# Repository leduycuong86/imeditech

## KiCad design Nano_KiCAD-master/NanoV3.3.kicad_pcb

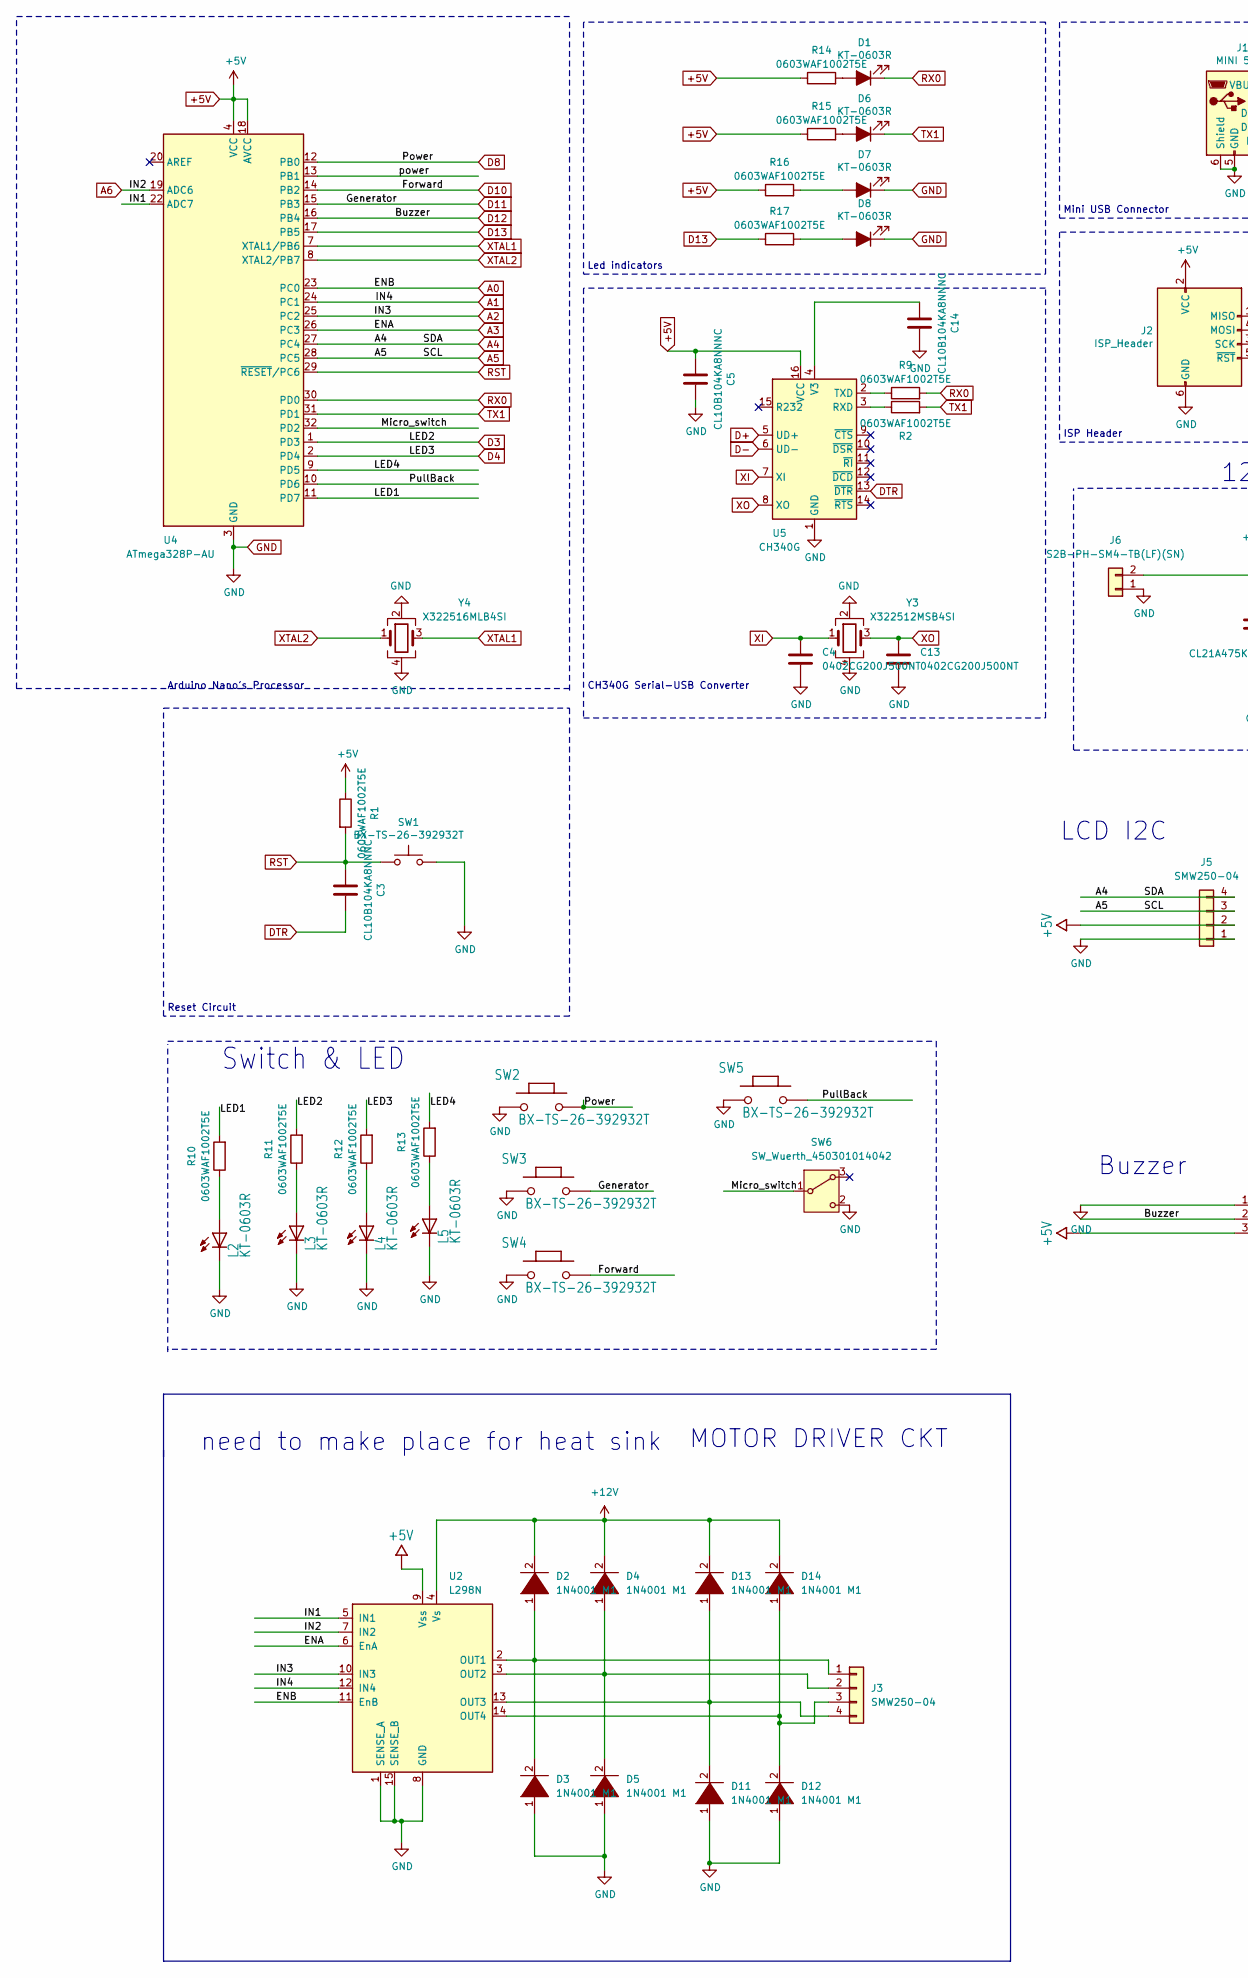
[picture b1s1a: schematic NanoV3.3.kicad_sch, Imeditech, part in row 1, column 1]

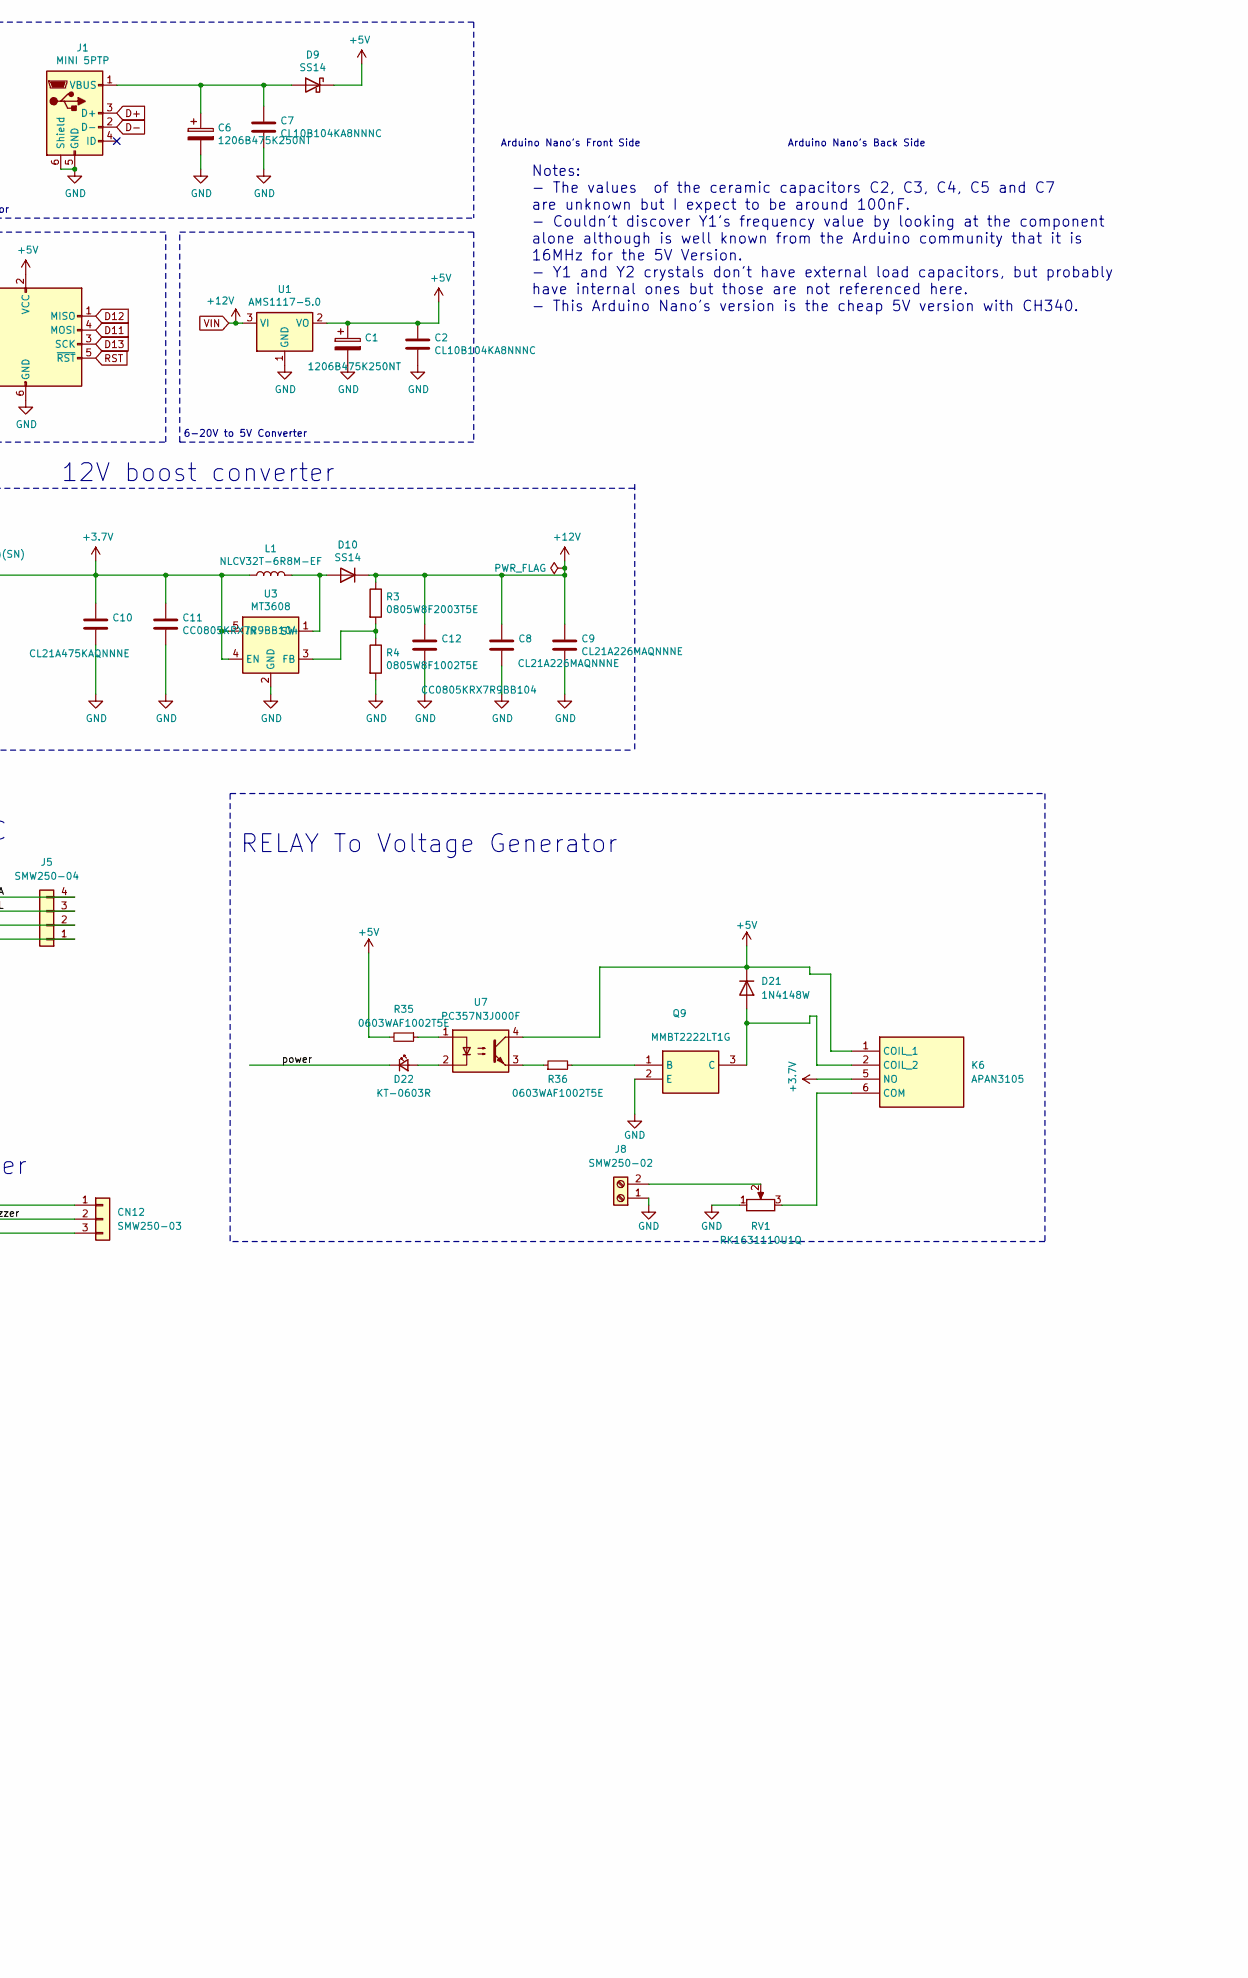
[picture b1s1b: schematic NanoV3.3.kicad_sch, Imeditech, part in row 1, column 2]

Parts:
C1, C6: 1206B475K250NT; CP_EIA-3216-10_Kemet-I
C2, C3, C5, C7, C14: CL10B104KA8NNNC; C_0603_1608Metric
C4, C13: 0402CG200J500NT; C_0402_1005Metric
C8, C9: CL21A226MAQNNNE; C_0805_2012Metric_Pad1.18x1.45mm_HandSolder
C10: CL21A475KAQNNNE; C_0805_2012Metric_Pad1.18x1.45mm_HandSolder
C11, C12: CC0805KRX7R9BB104; C_0805_2012Metric_Pad1.18x1.45mm_HandSolder
CN12: SMW250-03; JST_XH_B3B-XH-AM_1x03_P2.50mm_Vertical
D1, D6, D7, D8: KT-0603R; LED_0603_1608Metric_Pad1.05x0.95mm_HandSolder
D2, D3, D4, D5, D11, D12, D13, D14: 1N4001 M1; D_SMA
D9, D10: SS14; D_SOD-123
D21: 1N4148W; D_SOD-123
D22: KT-0603R; LED_0805_2012Metric_Pad1.15x1.40mm_HandSolder
J1: MINI 5PTP; USB_Mini-B_Lumberg_2486_01_Horizontal
J2: ISP_Header; PinHeader_2x03_P2.54mm_Vertical
J3, J5: SMW250-04; JST_XA_B04B-XASK-1-A_1x04_P2.50mm_Vertical
J6: S2B-PH-SM4-TB(LF)(SN); JST_PH_S2B-PH-SM4-TB_1x02-1MP_P2.00mm_Horizontal
J8: SMW250-02; JST_XA_B02B-XASK-1-A_1x02_P2.50mm_Vertical
K6: APAN3105; Mouser Part Number 769-APAN3105
L1: NLCV32T-6R8M-EF; L_1210_3225Metric_Pad1.42x2.65mm_HandSolder
L2, L3, L4, L5: KT-0603R; LED_0603_1608Metric_Pad1.05x0.95mm_HandSolder
Q9: MMBT2222LT1G; SOT96P237X111-3N; Mouser Part Number 863-MMBT2222LT1G
R1, R2, R9, R10, R11, R12, R13, R14, R15, R16, R17: 0603WAF1002T5E; R_0603_1608Metric
R3: 0805W8F2003T5E; R_0805_2012Metric_Pad1.20x1.40mm_HandSolder
R4: 0805W8F1002T5E; R_0805_2012Metric_Pad1.20x1.40mm_HandSolder
R35, R36: 0603WAF1002T5E; R_0805_2012Metric_Pad1.20x1.40mm_HandSolder
RV1: RK1631110U1Q; Potentiometer_Piher_PC-16_Single_Horizontal
SW1, SW2, SW3, SW4, SW5: BX-TS-26-392932T; SW_SPST_3.9x2.9mm
SW6: SW_Wuerth_450301014042; SW_XKB_DM1-16UD-1
U1: AMS1117-5.0; SOT-223
U2: L298N; TO-220-15_P2.54x2.54mm_StaggerOdd_Lead4.58mm_Vertical
U3: MT3608; SOT-23-6_Handsoldering
U4: ATmega328P-AU; TQFP-32_7x7mm_P0.8mm
U5: CH340G; SOIC-16_3.9x9.9mm_P1.27mm
U7: PC357N3J000F; SOP254P675X300-4N
Y3: X322512MSB4SI; Crystal_SMD_3225-4Pin_3.2x2.5mm
Y4: X322516MLB4SI; Crystal_SMD_3225-4Pin_3.2x2.5mm

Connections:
+3.7V: C10.1, C11.1, J6.2, K6.5 (NO), L1.1, U3.4 (EN), U3.5 (IN)
+5V: C1.1, C2.1, C5.2, CN12.3, D9.1 (K), D21.1 (K), J2.2 (VCC), J5.2, K6.1 (COIL_1), R1.1, R14.1, R15.1, R16.1, R35.2, U1.2 (VO), U2.9 (Vss), U4.4 (VCC), U4.6 (VCC), U4.18 (AVCC), U5.16 (VCC), U7.4
/IN1: U2.5 (IN1), U4.22 (ADC7)
/LED1: R10.2, U4.11 (PD7)
/LED4: R13.2, U4.9 (PD5)
/Micro_switch: SW6.1 (B), U4.32 (PD2)
/PullBack: SW5.2, U4.10 (PD6)
/power: D22.1 (K), U4.13 (PB1)
A0: U2.11 (EnB), U4.23 (PC0)
A1: U2.12 (IN4), U4.24 (PC1)
A2: U2.10 (IN3), U4.25 (PC2)
A3: U2.6 (EnA), U4.26 (PC3)
A4: J5.4, U4.27 (PC4)
A5: J5.3, U4.28 (PC5)
A6: U2.7 (IN2), U4.19 (ADC6)
D3: R11.2, U4.1 (PD3)
D4: R12.2, U4.2 (PD4)
D8: SW2.2, U4.12 (PB0)
D10: SW4.2, U4.14 (PB2)
D11: J2.4 (MOSI), SW3.2, U4.15 (PB3)
D12: CN12.2, J2.1 (MISO), U4.16 (PB4)
D13: J2.3 (SCK), R17.1, U4.17 (PB5)
D+: J1.3 (D+), U5.5 (UD+)
D-: J1.2 (D-), U5.6 (UD-)
DTR: C3.2, U5.13 (~DTR)
GND: C1.2, C2.2, C4.2, C5.1, C6.2, C7.2, C8.2, C9.2, C10.2, C11.2, C12.2, C13.2, C14.1, CN12.1, D3.1 (K), D5.1 (K), D7.1 (K), D8.1 (K), D11.1 (K), D12.1 (K), J1.5 (GND), J1.6 (Shield), J2.6 (GND), J5.1, J6.1, J8.1, L2.2, L3.2, L4.2, L5.2, Q9.2 (E), R4.2, RV1.1, SW1.2, SW2.1, SW3.1, SW4.1, SW5.1, SW6.2 (C), U1.1 (GND), U2.1 (SENSE_A), U2.8 (GND), U2.15 (SENSE_B), U3.2 (GND), U4.3 (GND), U4.5 (GND), U4.21 (GND), U5.1 (GND), Y3.2, Y3.4, Y4.2, Y4.4
unnamed: D1.2 (A), R14.2
unnamed: D2.1 (K), D3.2 (A), J3.1, U2.2 (OUT1)
unnamed: D4.1 (K), D5.2 (A), J3.2, U2.3 (OUT2)
unnamed: D6.2 (A), R15.2
unnamed: D7.2 (A), R16.2
unnamed: D8.2 (A), R17.2
unnamed: C6.1, C7.1, D9.2 (A), J1.1 (VBUS)
unnamed: D10.2 (A), L1.2, U3.1 (SW)
unnamed: D11.2 (A), D13.1 (K), J3.4, U2.13 (OUT3)
unnamed: D12.2 (A), D14.1 (K), J3.3, U2.14 (OUT4)
unnamed: D21.2 (A), K6.2 (COIL_2), Q9.3 (C)
unnamed: D22.2 (A), U7.2
unnamed: J8.2, RV1.2
unnamed: K6.6 (COM), RV1.3
unnamed: L2.1, R10.1
unnamed: L3.1, R11.1
unnamed: L4.1, R12.1
unnamed: L5.1, R13.1
unnamed: Q9.1 (B), R36.2
unnamed: R35.1, U7.1
unnamed: R36.1, U7.3
unnamed: R3.2, R4.1, U3.3 (FB)
unnamed: R2.1, U5.3 (RXD)
unnamed: R9.1, U5.2 (TXD)
unnamed: C14.2, U5.4 (V3)
RST: C3.1, J2.5 (~RST), R1.2, SW1.1, U4.29 (~RESET/PC6)
RX0: D1.1 (K), R9.2, U4.30 (PD0)
TX1: D6.1 (K), R2.2, U4.31 (PD1)
VIN: C8.1, C9.1, C12.1, D2.2 (A), D4.2 (A), D10.1 (K), D13.2 (A), D14.2 (A), R3.1, U1.3 (VI), U2.4 (Vs)
XI: C4.1, U5.7 (XI), Y3.1
XO: C13.1, U5.8 (XO), Y3.3
XTAL1: U4.7 (XTAL1/PB6), Y4.3
XTAL2: U4.8 (XTAL2/PB7), Y4.1

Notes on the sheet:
Reset Circuit
RELAY To Voltage Generator
6-20V to 5V Converter
Arduino Nano's Front Side
Notes: - The values of the ceramic capacitors C2, C3, C4, C5 and C7 are unknown but I expect to be around 100nF. - Couldn't discover Y1's frequency value by looking at the component alone although is well known from the Arduino community that it is 16MHz for the 5V Version. - Y1 and Y2 crystals don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
Buzzer
LCD I2C
need to make place for heat sink
Switch & LED
Arduino Nano's Back Side
ISP Header
CH340G Serial-USB Converter
Led indicators
12V boost converter
MOTOR DRIVER CKT
Mini USB Connector
Arduino Nano's Processor

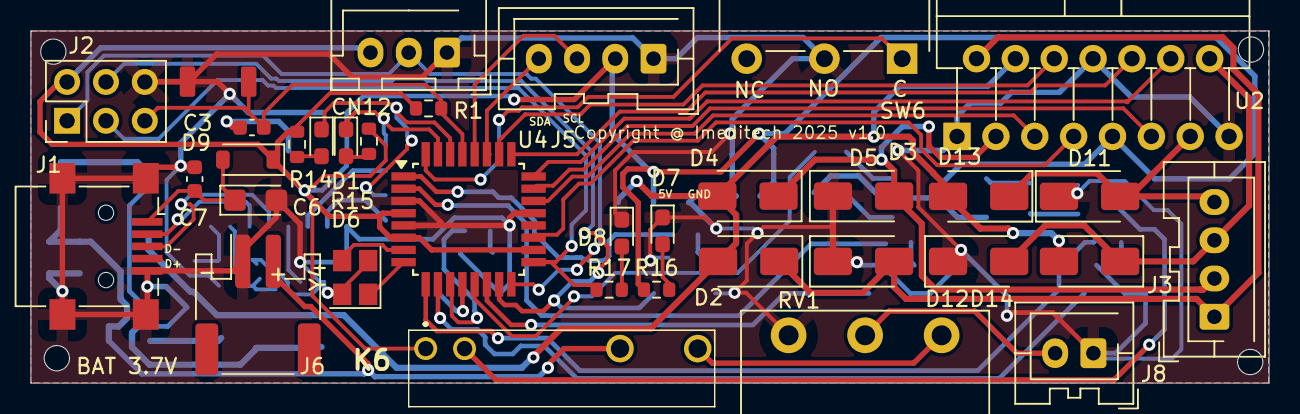
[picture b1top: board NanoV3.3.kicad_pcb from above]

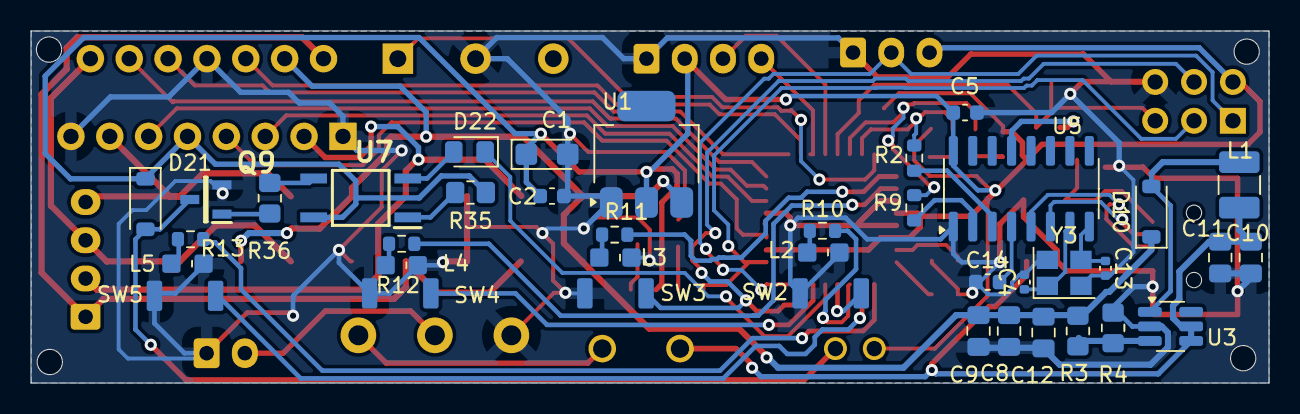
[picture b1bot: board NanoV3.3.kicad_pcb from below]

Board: 2 copper layers, 80.9 x 23.0 mm, 74 parts (39 on the bottom side), 59 nets.

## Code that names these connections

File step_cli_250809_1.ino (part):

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// Motor control pins (L298N)
const int IN1 = A7;    // ADC7
const int IN2 = A6;    // ADC6
const int ENA = A3;    // PC3
const int IN3 = A2;    // PC2
const int IN4 = A1;    // PC1
const int ENB = A0;    // PC0

// Button pins
const int BTN_FORWARD = 10;   // PB2 SW4
const int BTN_BACKWARD = 6;   // PD6 SW5
const int BTN_POWER = 8;   // PB0


// Thêm biến trạng thái cho các nút (thêm vào phần khai báo biến toàn cục)
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bool backwardButtonActive = false; // Trạng thái nút backward

// Buzzer pin
const int BUZZER_PIN = 12;    // PB4

// Relay pin
const int RELAY_PIN = 9;      // PB1 (D9)

// Button debounce variables
const int buttonCount = 3; // Thêm nút BTN_POWER
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
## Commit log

2025-08-17 update pcb
2025-08-22 update sequence diagram

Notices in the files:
Nano_KiCAD-master/NanoV3.3.kicad_pcb:
Copyright @ Imeditech 2025 v1.0
